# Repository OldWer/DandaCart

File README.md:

# Dandanator Cartridge System
Most of us ZX Spectrum fans are well aware of the ZX Dandanator! Mini, a game cartridge for the Spectrum computers. It is a fine piece of hardware, the only problem is that the ROM quickly gets filled with games, especially if you want to play Multiload titles, and then there are some hard choices about what to keep and what to delete. This project, based on the idea of my fellow retro enthusiast Artur Grütz, aims to rectify it.

The DandaCart simply moves the onboard memory chip to a cartridge. The device remains fully compatible with the original Dandanator (including Multiply and joystick support). Now you can burn as many cartridges as you want and simply swap them out as necessary! There is also something very satisfying about inserting a real, physical cartridge to play a game.

One of the stated goals of the Dandanator project is to be “a platform for developing and releasing cartridge games”. Now, with a system of replaceable cartridges, this could become a reality!

This repository contains the KiCad projects for three PCBs: the base board (_DandaCartBase_) and two versions of the cartridge board (_DandaCartDIP_ and _DandaCartPLCC_). You can choose the cartridge PCB version based on the type of the SST39SF040 memory you have available (DIP-32 or PLCC-32); be aware, however, that the PLCC version is more difficult to solder, there is no PLCC socket in the design, because the cartridge would become too bulky then. The _Gerbers_ directory contains ZIPs ready for manufacturing — the cartridge PCBs are already panelized (six cartridge PCBs on one board).

## See DandaCart in action
[Youtube Video](https://youtu.be/q8KvgayKHwo)

## Building the DandaCart
The Bill of Materials can be found in the _DandaCartBase/BOM_ directory and is almost the same as for the original Dandanator, only instead of the PLCC socket a 2x18pin edge card connector is used. As for the cartridge connector, when soldering it to the base board, two pins will have to be removed; I was originally planning for the cartridges to have a notch in the PCB and for the edge connector to have a keying tab, but I had run into difficulties with the notch on the panelized layout, so I finally decided for the cartridge housing itself to be keyed (to prevent incorrect insertion), but by then I had already routed quite a few traces through the gap, and with the cartridge slot running across the board it was really difficult to route all the traces to the rear expansion connector, so I decided to leave it like that.

The _3DModels_ directory contains STL files for printing the base board enclosure and the cartridge enclosure. There is also the _Label_ directory with a label for the cartridges (to be printed on self-adhesive 10x15 cm photo paper).

All the software, such as .hex and .jed files for programming the onboard microcontroller and the GAL chip, manuals etc. are available at the Dandanator site:
http://www.dandare.es/Proyectos_Dandare/Proyectos.html

The Multiply expansion Github repository is available at:
https://github.com/mad3001/Multiply

## License
LICENSE: CC BY-SA 4.0
https://creativecommons.org/licenses/by-sa/4.0/

## Acknowledgements
Of course, full credits go to Dandare, the creator of the original Dandanator, as well as Mad3001 and OverCLK, the co-creators of the Multiply expansion. All I did was some PCB routing and some light CAD work. Special thanks to Artur Grütz for his idea of replaceable cartridges!

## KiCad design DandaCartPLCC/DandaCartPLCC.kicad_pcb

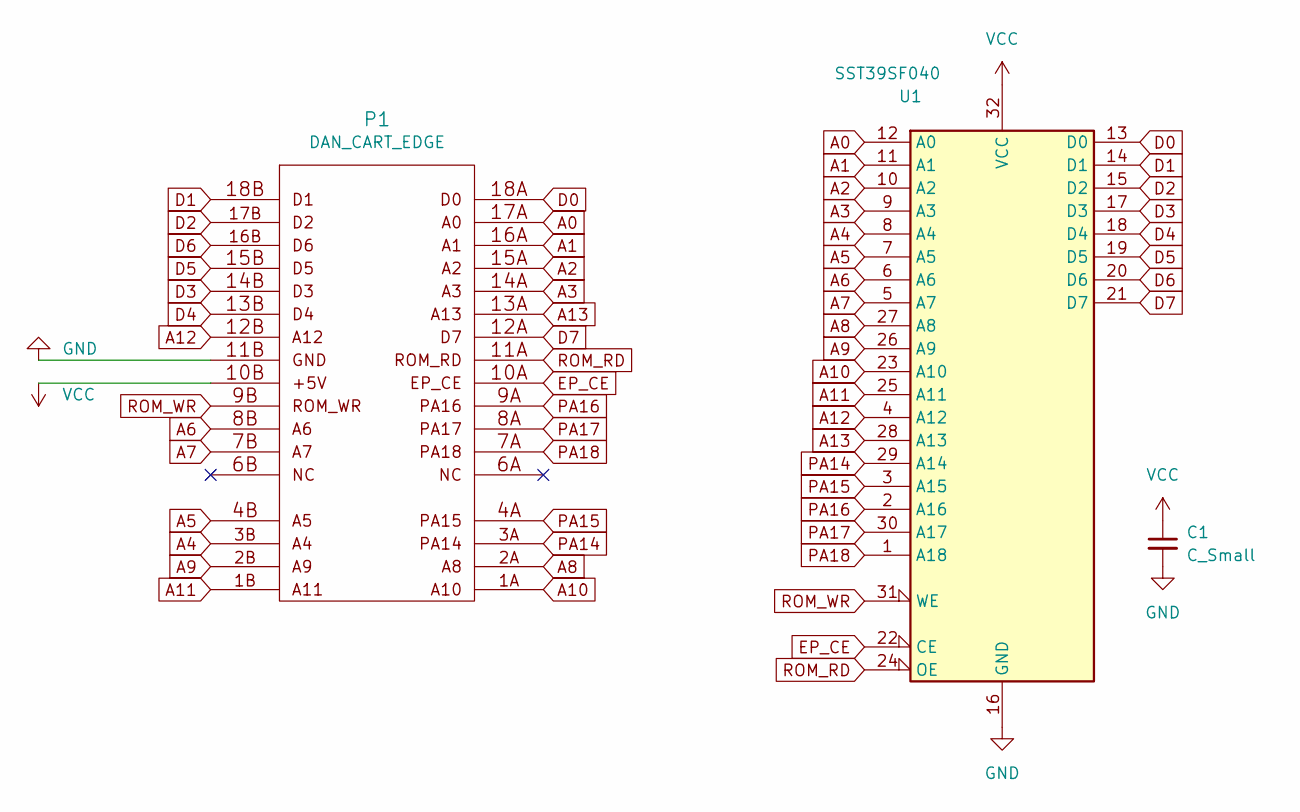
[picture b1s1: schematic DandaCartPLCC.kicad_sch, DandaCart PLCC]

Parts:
C1: C_Small; C_0805_2012Metric_Pad1.18x1.45mm_HandSolder
P1: DAN_CART_EDGE; DAN_CART_BUS
U1: SST39SF040; PLCC-32_11.4x14.0mm_P1.27mm

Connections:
A0: P1.17A (WE#), U1.12 (A0)
A1: P1.16A (A17), U1.11 (A1)
A2: P1.15A (A14), U1.10 (A2)
A3: P1.14A (A13), U1.9 (A3)
A4: P1.3B (DQ1), U1.8 (A4)
A5: P1.4B (DQ0), U1.7 (A5)
A6: P1.8B (A1), U1.6 (A6)
A7: P1.7B (A0), U1.5 (A7)
A8: P1.2A (DQ4), U1.27 (A8)
A9: P1.2B (DQ2), U1.26 (A9)
A10: P1.1A (DQ3), U1.23 (A10)
A11: P1.1B (GND), U1.25 (A11)
A12: P1.12B (A5), U1.4 (A12)
A13: P1.13A (A8), U1.28 (A13)
D0: P1.18A (+5V), U1.13 (D0)
D1: P1.18B (A18), U1.14 (D1)
D2: P1.17B (A16), U1.15 (D2)
D3: P1.14B (A7), U1.17 (D3)
D4: P1.13B (A6), U1.18 (D4)
D5: P1.15B (A12), U1.19 (D5)
D6: P1.16B (A15), U1.20 (D6)
D7: P1.12A (A9), U1.21 (D7)
EP_CE: P1.10A (OE#), U1.22 (CE)
GND: C1.2, P1.11B (A4), U1.16 (GND)
PA14: P1.3A (DQ5), U1.29 (A14)
PA15: P1.4A (DQ6), U1.3 (A15)
PA16: P1.9A (A10), U1.2 (A16)
PA17: P1.8A (CE#), U1.30 (A17)
PA18: P1.7A (DQ7), U1.1 (A18)
ROM_RD: P1.11A (A11), U1.24 (OE)
ROM_WR: P1.9B (A2), U1.31 (WE)
VCC: C1.1, P1.10B (A3), U1.32 (VCC)

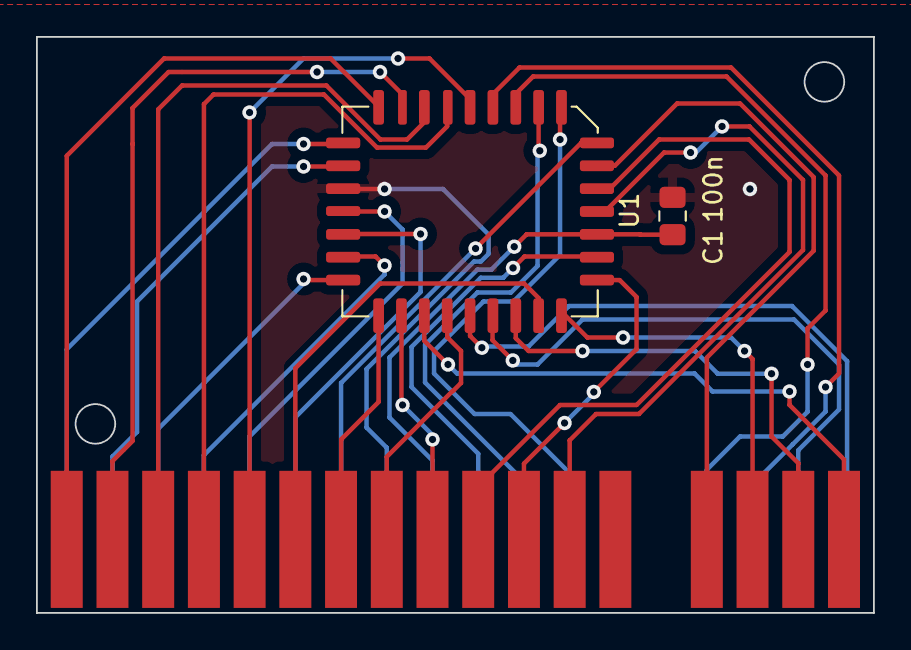
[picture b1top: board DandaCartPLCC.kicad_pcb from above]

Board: 2 copper layers, 46.5 x 32.0 mm, 3 parts (1 on the bottom side), 32 nets.

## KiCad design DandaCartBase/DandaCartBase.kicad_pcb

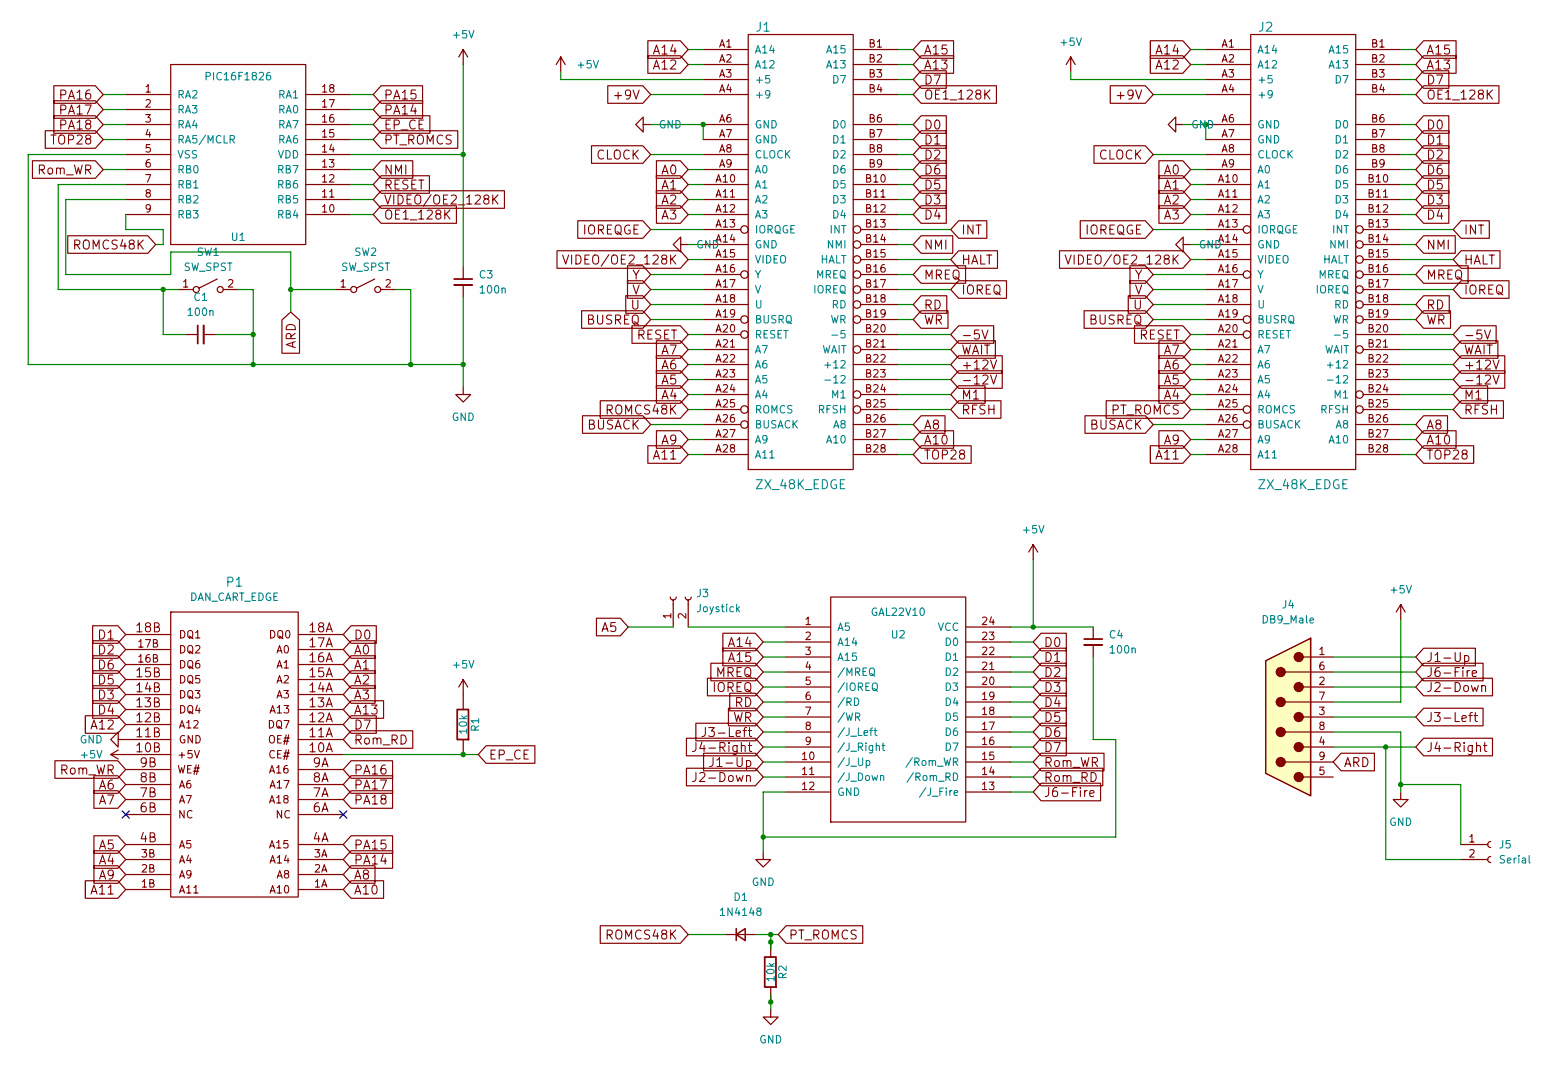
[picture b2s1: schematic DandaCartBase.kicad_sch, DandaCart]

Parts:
C1, C3, C4: 100n; C_Disc_D5.0mm_W2.5mm_P2.50mm
D1: 1N4148; D_DO-35_SOD27_P7.62mm_Horizontal
J1: ZX_48K_EDGE; ZX_CONN
J2: ZX_48K_EDGE; ZX_BUS
J3: Joystick; PinHeader_1x02_P2.54mm_Vertical
J4: DB9_Male; DB_9M
J5: Serial; PinHeader_1x02_P2.54mm_Vertical
P1: DAN_CART_EDGE
R1, R2: 10k; RC03
SW1, SW2: SW_SPST; SW_PUSH_6mm
U1: PIC16F1826; DIP-18_W7.62mm_LongPads
U2: GAL22V10; DIP-24_W7.62mm_LongPads

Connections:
+5V: C3.1, C4.1, J1.A3 (+5), J2.A3 (+5), J4.7, P1.10B (A3), R1.1, U1.14 (VDD), U2.24 (VCC)
+9V: J1.A4 (+9), J2.A4 (+9)
+12V: J1.B22 (+12), J2.B22 (+12)
-5V: J1.B20 (-5), J2.B20 (-5)
-12V: J1.B23 (-12), J2.B23 (-12)
A0: J1.A9 (A0), J2.A9 (A0), P1.17A (WE#)
A1: J1.A10 (A1), J2.A10 (A1), P1.16A (A17)
A2: J1.A11 (A2), J2.A11 (A2), P1.15A (A14)
A3: J1.A12 (A3), J2.A12 (A3), P1.14A (A13)
A4: J1.A24 (A4), J2.A24 (A4), P1.3B (DQ1)
A5: J1.A23 (A5), J2.A23 (A5), J3.1, P1.4B (DQ0)
A6: J1.A22 (A6), J2.A22 (A6), P1.8B (A1)
A7: J1.A21 (A7), J2.A21 (A7), P1.7B (A0)
A8: J1.B26 (A8), J2.B26 (A8), P1.2A (DQ4)
A9: J1.A27 (A9), J2.A27 (A9), P1.2B (DQ2)
A10: J1.B27 (A10), J2.B27 (A10), P1.1A (DQ3)
A11: J1.A28 (A11), J2.A28 (A11), P1.1B (GND)
A12: J1.A2 (A12), J2.A2 (A12), P1.12B (A5)
A13: J1.B2 (A13), J2.B2 (A13), P1.13A (A8)
A14: J1.A1 (A14), J2.A1 (A14), U2.2 (A14)
A15: J1.B1 (A15), J2.B1 (A15), U2.3 (A15)
ARD: J4.9, SW2.1 (A), U1.8 (RB2)
BUSACK: J1.A26 (BUSACK), J2.A26 (BUSACK)
BUSREQ: J1.A19 (BUSRQ), J2.A19 (BUSRQ)
CLOCK: J1.A8 (CLOCK), J2.A8 (CLOCK)
D0: J1.B6 (D0), J2.B6 (D0), P1.18A (+5V), U2.23 (D0)
D1: J1.B7 (D1), J2.B7 (D1), P1.18B (A18), U2.22 (D1)
D2: J1.B8 (D2), J2.B8 (D2), P1.17B (A16), U2.21 (D2)
D3: J1.B11 (D3), J2.B11 (D3), P1.14B (A7), U2.20 (D3)
D4: J1.B12 (D4), J2.B12 (D4), P1.13B (A6), U2.19 (D4)
D5: J1.B10 (D5), J2.B10 (D5), P1.15B (A12), U2.18 (D5)
D6: J1.B9 (D6), J2.B9 (D6), P1.16B (A15), U2.17 (D6)
D7: J1.B3 (D7), J2.B3 (D7), P1.12A (A9), U2.16 (D7)
EP_CE: P1.10A (OE#), R1.2, U1.16 (RA7)
GND: C1.2, C3.2, C4.2, J1.A6 (GND), J1.A7 (GND), J1.A14 (GND), J2.A6 (GND), J2.A7 (GND), J2.A14 (GND), J4.8, J5.1, P1.11B (A4), R2.2, SW1.2 (B), SW2.2 (B), U1.5 (VSS), U2.12 (GND)
HALT: J1.B15 (HALT), J2.B15 (HALT)
INT: J1.B13 (INT), J2.B13 (INT)
IOREQ: J1.B17 (IOREQ), J2.B17 (IOREQ), U2.5 (/IOREQ)
IOREQGE: J1.A13 (IORQGE), J2.A13 (IORQGE)
J1-Up: J4.1, U2.10 (/J_Up)
J2-Down: J4.2, U2.11 (/J_Down)
J3-Left: J4.3, U2.8 (/J_Left)
J4-Right: J4.4, J5.2, U2.9 (/J_Right)
J6-Fire: J4.6, U2.13 (/J_Fire)
M1: J1.B24 (M1), J2.B24 (M1)
MREQ: J1.B16 (MREQ), J2.B16 (MREQ), U2.4 (/MREQ)
NMI: J1.B14 (NMI), J2.B14 (NMI), U1.13 (RB7)
unnamed: C1.1, SW1.1 (A), U1.7 (RB1)
unnamed: J3.2, U2.1 (A5)
OE1_128K: J1.B4, J2.B4, U1.10 (RB4)
PA14: P1.3A (DQ5), U1.17 (RA0)
PA15: P1.4A (DQ6), U1.18 (RA1)
PA16: P1.9A (A10), U1.1 (RA2)
PA17: P1.8A (CE#), U1.2 (RA3)
PA18: P1.7A (DQ7), U1.3 (RA4)
PT_ROMCS: D1.2 (A), J2.A25 (ROMCS), R2.1, U1.15 (RA6)
RD: J1.B18 (RD), J2.B18 (RD), U2.6 (/RD)
RESET: J1.A20 (RESET), J2.A20 (RESET), U1.12 (RB6)
RFSH: J1.B25 (RFSH), J2.B25 (RFSH)
ROMCS48K: D1.1 (K), J1.A25 (ROMCS), U1.9 (RB3)
Rom_RD: P1.11A (A11), U2.14 (/Rom_RD)
Rom_WR: P1.9B (A2), U1.6 (RB0), U2.15 (/Rom_WR)
TOP28: J1.B28, J2.B28, U1.4 (RA5/MCLR)
U: J1.A18 (U), J2.A18 (U)
V: J1.A17 (V), J2.A17 (V)
VIDEO/OE2_128K: J1.A15 (VIDEO), J2.A15 (VIDEO), U1.11 (RB5)
WAIT: J1.B21 (WAIT), J2.B21 (WAIT)
WR: J1.B19 (WR), J2.B19 (WR), U2.7 (/WR)
Y: J1.A16 (Y), J2.A16 (Y)

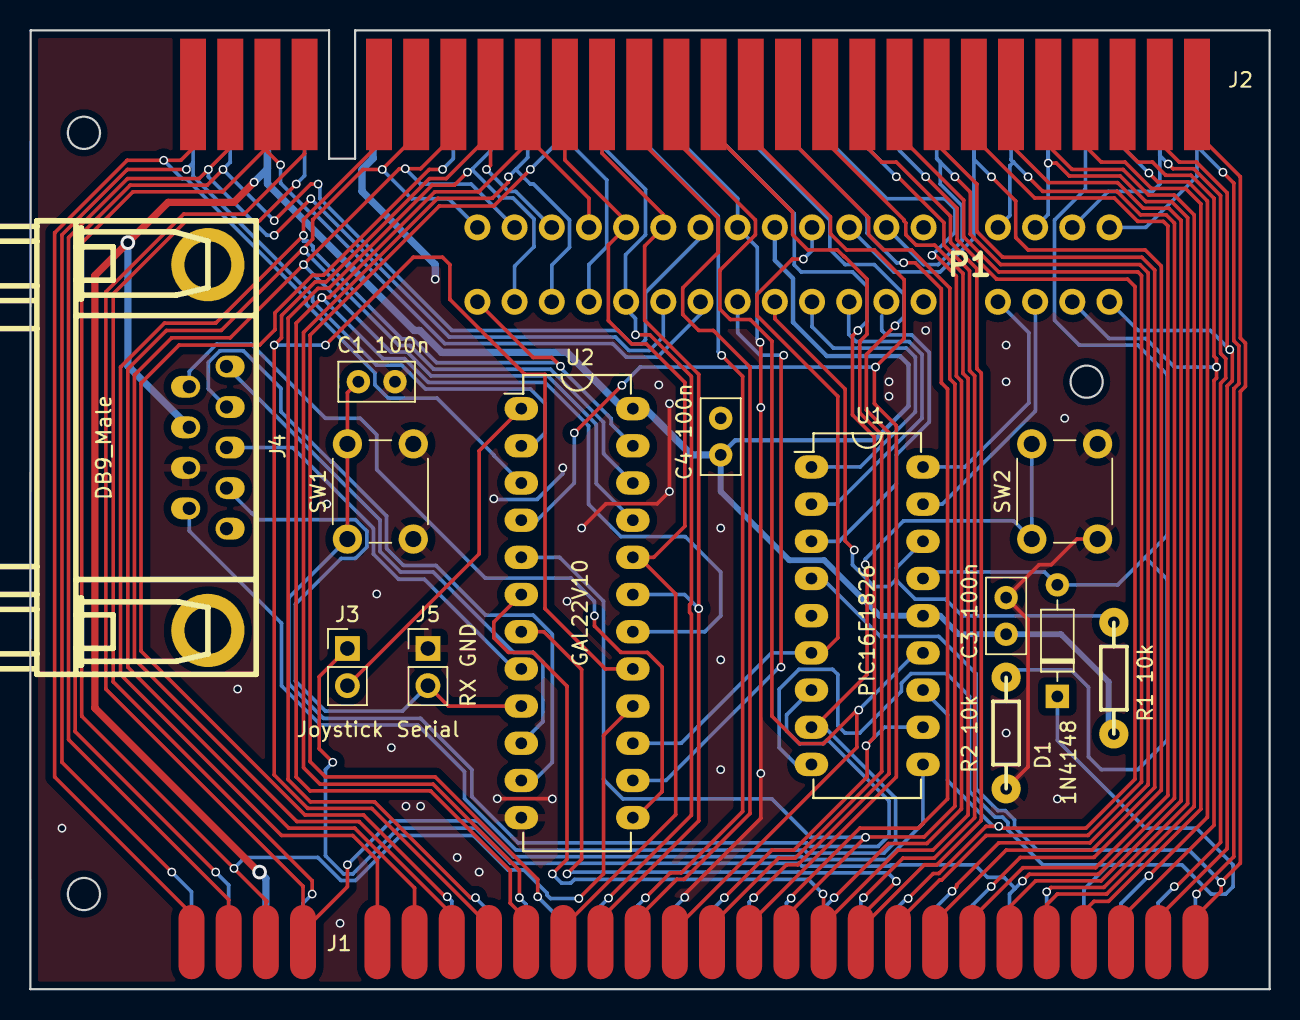
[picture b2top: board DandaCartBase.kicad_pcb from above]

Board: 2 copper layers, 84.7 x 65.5 mm, 16 parts (0 on the bottom side), 69 nets.

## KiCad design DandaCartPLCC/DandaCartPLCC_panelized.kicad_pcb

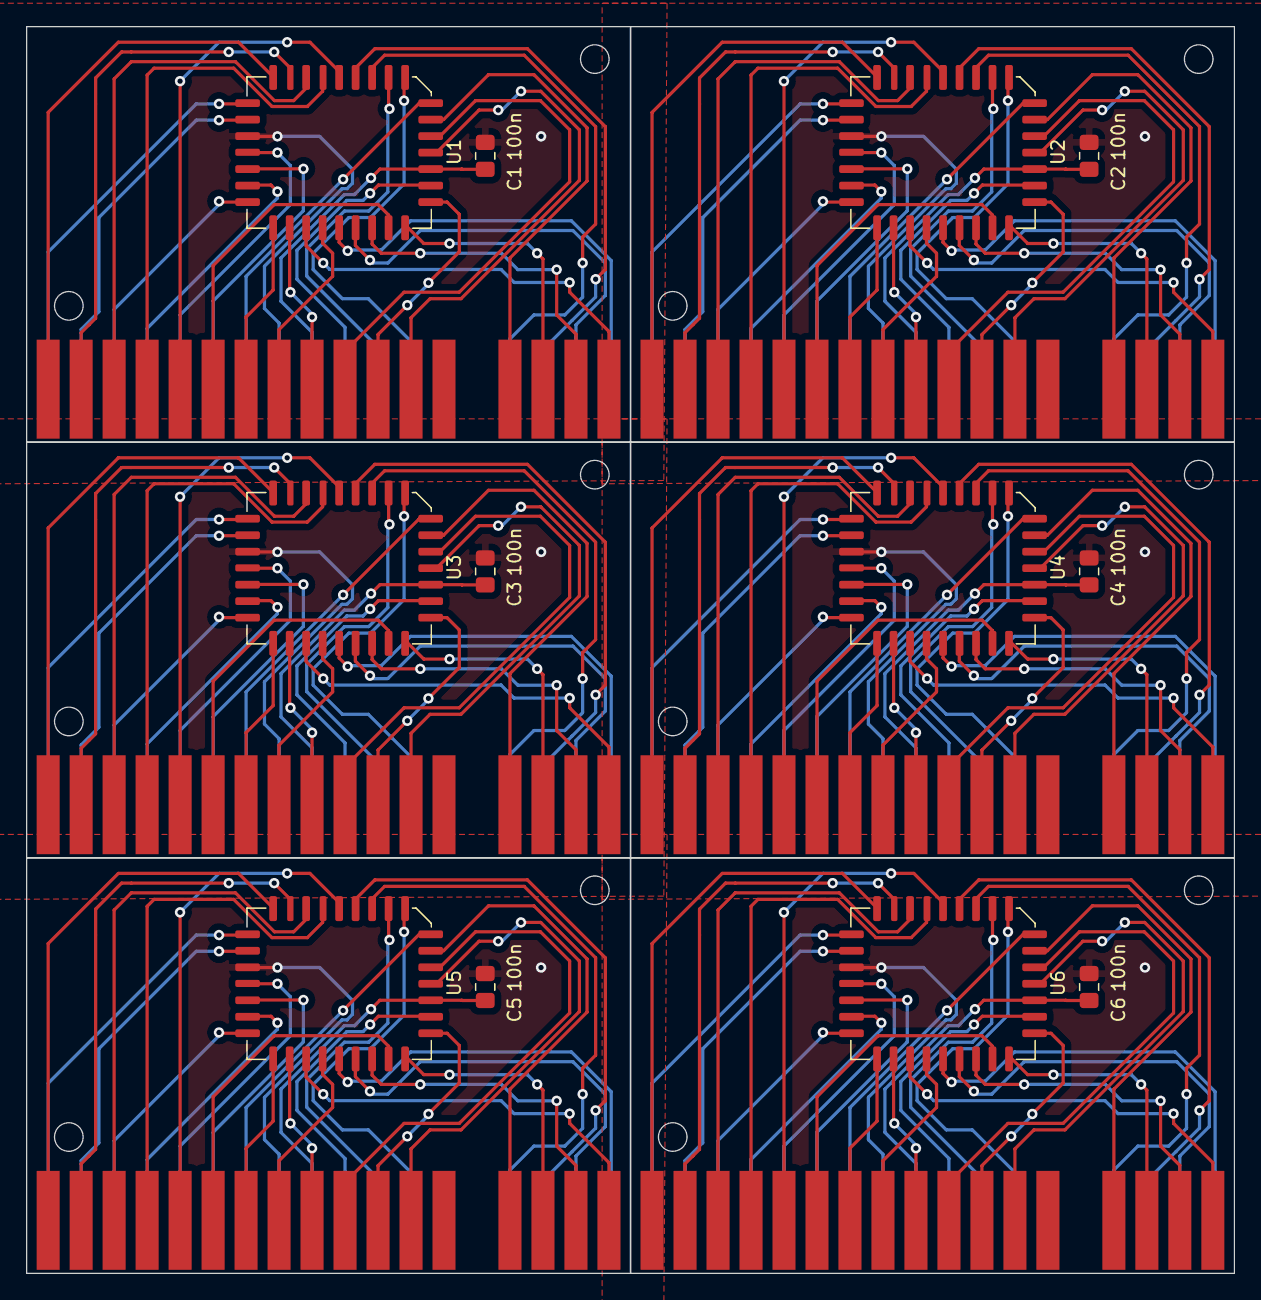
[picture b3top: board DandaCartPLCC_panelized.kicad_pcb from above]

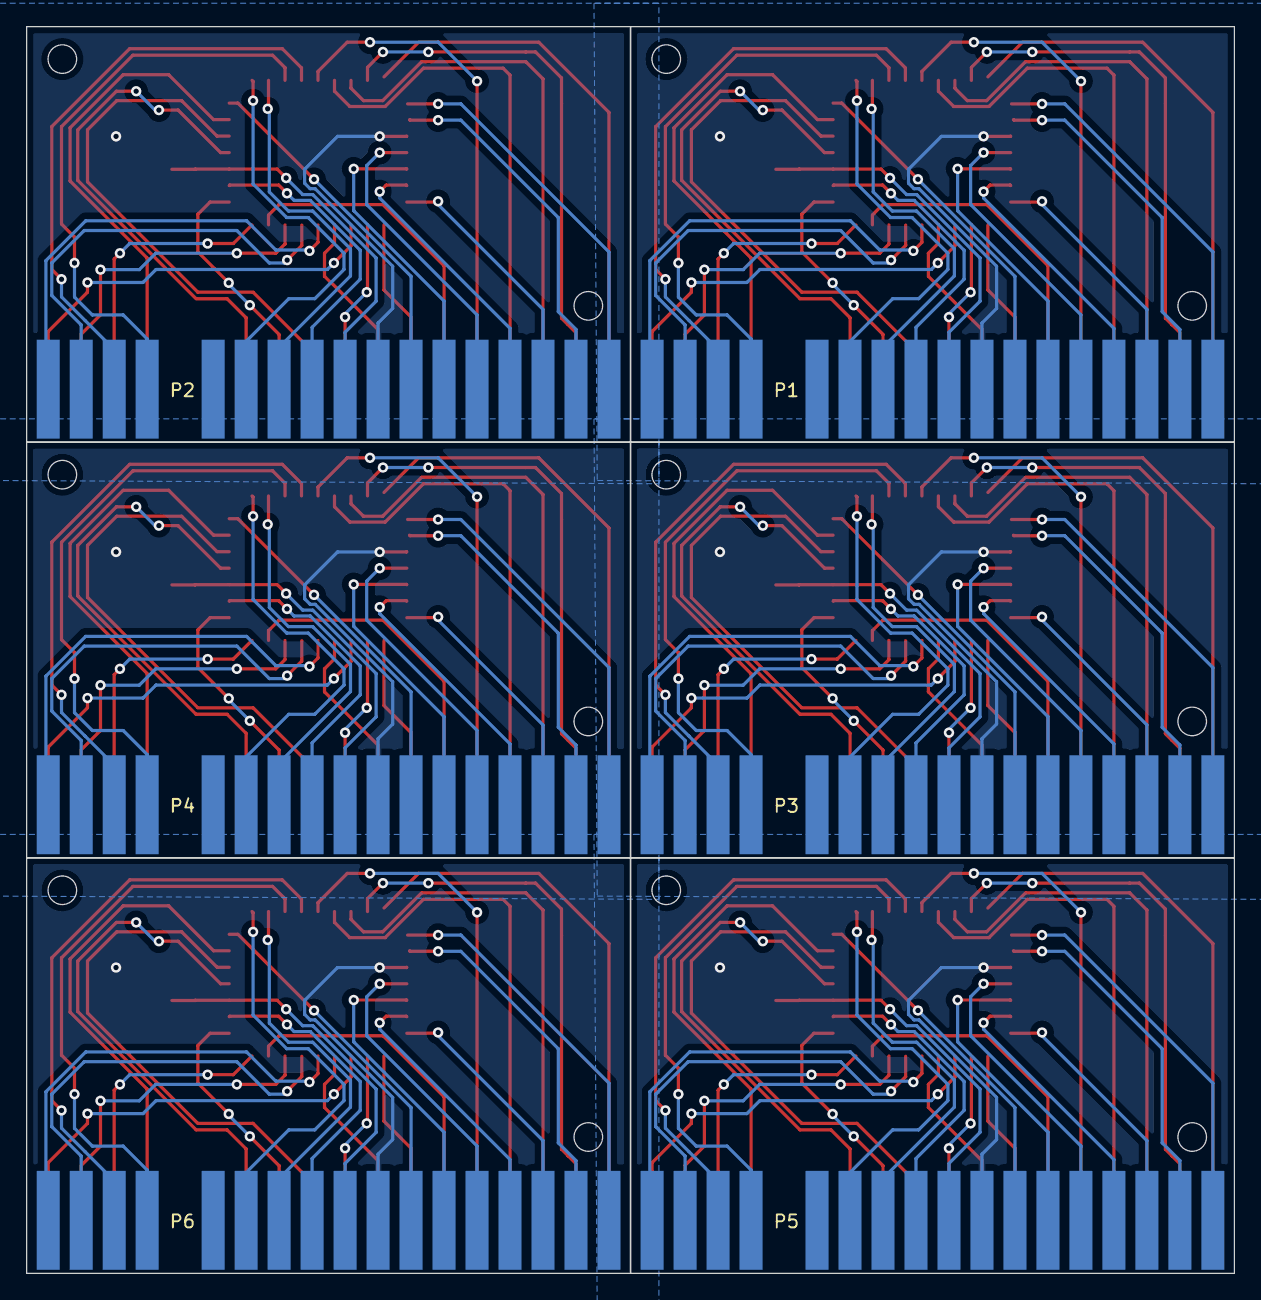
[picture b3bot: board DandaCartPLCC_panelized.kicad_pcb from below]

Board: 2 copper layers, 93.0 x 96.0 mm, 18 parts (6 on the bottom side), 32 nets.

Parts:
C1, C2, C3, C4, C5, C6: C_Small; C_0805_2012Metric_Pad1.18x1.45mm_HandSolder
P1, P2, P3, P4, P5, P6: DAN_CART_EDGE; DAN_CART_BUS
U1, U2, U3, U4, U5, U6: SST39SF040; PLCC-32_11.4x14.0mm_P1.27mm

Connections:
A0: P1.17A (WE#), P2.17A (WE#), P3.17A (WE#), P4.17A (WE#), P5.17A (WE#), P6.17A (WE#), U1.12 (A0), U2.12 (A0), U3.12 (A0), U4.12 (A0), U5.12 (A0), U6.12 (A0)
A1: P1.16A (A17), P2.16A (A17), P3.16A (A17), P4.16A (A17), P5.16A (A17), P6.16A (A17), U1.11 (A1), U2.11 (A1), U3.11 (A1), U4.11 (A1), U5.11 (A1), U6.11 (A1)
A2: P1.15A (A14), P2.15A (A14), P3.15A (A14), P4.15A (A14), P5.15A (A14), P6.15A (A14), U1.10 (A2), U2.10 (A2), U3.10 (A2), U4.10 (A2), U5.10 (A2), U6.10 (A2)
A3: P1.14A (A13), P2.14A (A13), P3.14A (A13), P4.14A (A13), P5.14A (A13), P6.14A (A13), U1.9 (A3), U2.9 (A3), U3.9 (A3), U4.9 (A3), U5.9 (A3), U6.9 (A3)
A4: P1.3B (DQ1), P2.3B (DQ1), P3.3B (DQ1), P4.3B (DQ1), P5.3B (DQ1), P6.3B (DQ1), U1.8 (A4), U2.8 (A4), U3.8 (A4), U4.8 (A4), U5.8 (A4), U6.8 (A4)
A5: P1.4B (DQ0), P2.4B (DQ0), P3.4B (DQ0), P4.4B (DQ0), P5.4B (DQ0), P6.4B (DQ0), U1.7 (A5), U2.7 (A5), U3.7 (A5), U4.7 (A5), U5.7 (A5), U6.7 (A5)
A6: P1.8B (A1), P2.8B (A1), P3.8B (A1), P4.8B (A1), P5.8B (A1), P6.8B (A1), U1.6 (A6), U2.6 (A6), U3.6 (A6), U4.6 (A6), U5.6 (A6), U6.6 (A6)
A7: P1.7B (A0), P2.7B (A0), P3.7B (A0), P4.7B (A0), P5.7B (A0), P6.7B (A0), U1.5 (A7), U2.5 (A7), U3.5 (A7), U4.5 (A7), U5.5 (A7), U6.5 (A7)
A8: P1.2A (DQ4), P2.2A (DQ4), P3.2A (DQ4), P4.2A (DQ4), P5.2A (DQ4), P6.2A (DQ4), U1.27 (A8), U2.27 (A8), U3.27 (A8), U4.27 (A8), U5.27 (A8), U6.27 (A8)
A9: P1.2B (DQ2), P2.2B (DQ2), P3.2B (DQ2), P4.2B (DQ2), P5.2B (DQ2), P6.2B (DQ2), U1.26 (A9), U2.26 (A9), U3.26 (A9), U4.26 (A9), U5.26 (A9), U6.26 (A9)
A10: P1.1A (DQ3), P2.1A (DQ3), P3.1A (DQ3), P4.1A (DQ3), P5.1A (DQ3), P6.1A (DQ3), U1.23 (A10), U2.23 (A10), U3.23 (A10), U4.23 (A10), U5.23 (A10), U6.23 (A10)
A11: P1.1B (GND), P2.1B (GND), P3.1B (GND), P4.1B (GND), P5.1B (GND), P6.1B (GND), U1.25 (A11), U2.25 (A11), U3.25 (A11), U4.25 (A11), U5.25 (A11), U6.25 (A11)
A12: P1.12B (A5), P2.12B (A5), P3.12B (A5), P4.12B (A5), P5.12B (A5), P6.12B (A5), U1.4 (A12), U2.4 (A12), U3.4 (A12), U4.4 (A12), U5.4 (A12), U6.4 (A12)
A13: P1.13A (A8), P2.13A (A8), P3.13A (A8), P4.13A (A8), P5.13A (A8), P6.13A (A8), U1.28 (A13), U2.28 (A13), U3.28 (A13), U4.28 (A13), U5.28 (A13), U6.28 (A13)
D0: P1.18A (+5V), P2.18A (+5V), P3.18A (+5V), P4.18A (+5V), P5.18A (+5V), P6.18A (+5V), U1.13 (D0), U2.13 (D0), U3.13 (D0), U4.13 (D0), U5.13 (D0), U6.13 (D0)
D1: P1.18B (A18), P2.18B (A18), P3.18B (A18), P4.18B (A18), P5.18B (A18), P6.18B (A18), U1.14 (D1), U2.14 (D1), U3.14 (D1), U4.14 (D1), U5.14 (D1), U6.14 (D1)
D2: P1.17B (A16), P2.17B (A16), P3.17B (A16), P4.17B (A16), P5.17B (A16), P6.17B (A16), U1.15 (D2), U2.15 (D2), U3.15 (D2), U4.15 (D2), U5.15 (D2), U6.15 (D2)
D3: P1.14B (A7), P2.14B (A7), P3.14B (A7), P4.14B (A7), P5.14B (A7), P6.14B (A7), U1.17 (D3), U2.17 (D3), U3.17 (D3), U4.17 (D3), U5.17 (D3), U6.17 (D3)
D4: P1.13B (A6), P2.13B (A6), P3.13B (A6), P4.13B (A6), P5.13B (A6), P6.13B (A6), U1.18 (D4), U2.18 (D4), U3.18 (D4), U4.18 (D4), U5.18 (D4), U6.18 (D4)
D5: P1.15B (A12), P2.15B (A12), P3.15B (A12), P4.15B (A12), P5.15B (A12), P6.15B (A12), U1.19 (D5), U2.19 (D5), U3.19 (D5), U4.19 (D5), U5.19 (D5), U6.19 (D5)
D6: P1.16B (A15), P2.16B (A15), P3.16B (A15), P4.16B (A15), P5.16B (A15), P6.16B (A15), U1.20 (D6), U2.20 (D6), U3.20 (D6), U4.20 (D6), U5.20 (D6), U6.20 (D6)
D7: P1.12A (A9), P2.12A (A9), P3.12A (A9), P4.12A (A9), P5.12A (A9), P6.12A (A9), U1.21 (D7), U2.21 (D7), U3.21 (D7), U4.21 (D7), U5.21 (D7), U6.21 (D7)
EP_CE: P1.10A (OE#), P2.10A (OE#), P3.10A (OE#), P4.10A (OE#), P5.10A (OE#), P6.10A (OE#), U1.22 (CE), U2.22 (CE), U3.22 (CE), U4.22 (CE), U5.22 (CE), U6.22 (CE)
GND: C1.2, C2.2, C3.2, C4.2, C5.2, C6.2, P1.11B (A4), P2.11B (A4), P3.11B (A4), P4.11B (A4), P5.11B (A4), P6.11B (A4), U1.16 (GND), U2.16 (GND), U3.16 (GND), U4.16 (GND), U5.16 (GND), U6.16 (GND)
PA14: P1.3A (DQ5), P2.3A (DQ5), P3.3A (DQ5), P4.3A (DQ5), P5.3A (DQ5), P6.3A (DQ5), U1.29 (A14), U2.29 (A14), U3.29 (A14), U4.29 (A14), U5.29 (A14), U6.29 (A14)
PA15: P1.4A (DQ6), P2.4A (DQ6), P3.4A (DQ6), P4.4A (DQ6), P5.4A (DQ6), P6.4A (DQ6), U1.3 (A15), U2.3 (A15), U3.3 (A15), U4.3 (A15), U5.3 (A15), U6.3 (A15)
PA16: P1.9A (A10), P2.9A (A10), P3.9A (A10), P4.9A (A10), P5.9A (A10), P6.9A (A10), U1.2 (A16), U2.2 (A16), U3.2 (A16), U4.2 (A16), U5.2 (A16), U6.2 (A16)
PA17: P1.8A (CE#), P2.8A (CE#), P3.8A (CE#), P4.8A (CE#), P5.8A (CE#), P6.8A (CE#), U1.30 (A17), U2.30 (A17), U3.30 (A17), U4.30 (A17), U5.30 (A17), U6.30 (A17)
PA18: P1.7A (DQ7), P2.7A (DQ7), P3.7A (DQ7), P4.7A (DQ7), P5.7A (DQ7), P6.7A (DQ7), U1.1 (A18), U2.1 (A18), U3.1 (A18), U4.1 (A18), U5.1 (A18), U6.1 (A18)
ROM_RD: P1.11A (A11), P2.11A (A11), P3.11A (A11), P4.11A (A11), P5.11A (A11), P6.11A (A11), U1.24 (OE), U2.24 (OE), U3.24 (OE), U4.24 (OE), U5.24 (OE), U6.24 (OE)
ROM_WR: P1.9B (A2), P2.9B (A2), P3.9B (A2), P4.9B (A2), P5.9B (A2), P6.9B (A2), U1.31 (WE), U2.31 (WE), U3.31 (WE), U4.31 (WE), U5.31 (WE), U6.31 (WE)
VCC: C1.1, C2.1, C3.1, C4.1, C5.1, C6.1, P1.10B (A3), P2.10B (A3), P3.10B (A3), P4.10B (A3), P5.10B (A3), P6.10B (A3), U1.32 (VCC), U2.32 (VCC), U3.32 (VCC), U4.32 (VCC), U5.32 (VCC), U6.32 (VCC)
